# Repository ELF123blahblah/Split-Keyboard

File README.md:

## Hardware
# PCB

# Schematics

# Note
The bottom one and the little rectangle will be printed with transparent PLA. To give it an underglow effect and make a window for the microcontrollers
I have the screws thats why i didnt include it in the BOM.
## Details
This hackpad is made to help me have a better time while programming, gaming and 3D printing things.
### BOM
- 9 Cherry MX Switches
- 12 SK6812 MINI LEDs
- 1 XIAO RP2040
- 9 Blank DSA Keycaps
- ~ 80g Normal PLA
- ~ 30g transparent PLA
Disclaimer:
The switches and the top part fits perfectly because of some issues on my macbook I can't upload the video/image onto my github repo so if you have any questions please contact me via slack so that I can show you how it is made myself and answer any questions
### My request for the staff:
Please don't require a full component assembled photo/file as it is way too much work that I need to remove all the stuff to print it and it didn't make a difference in the aligning part as well cause i just had to flip the top part and that's it.

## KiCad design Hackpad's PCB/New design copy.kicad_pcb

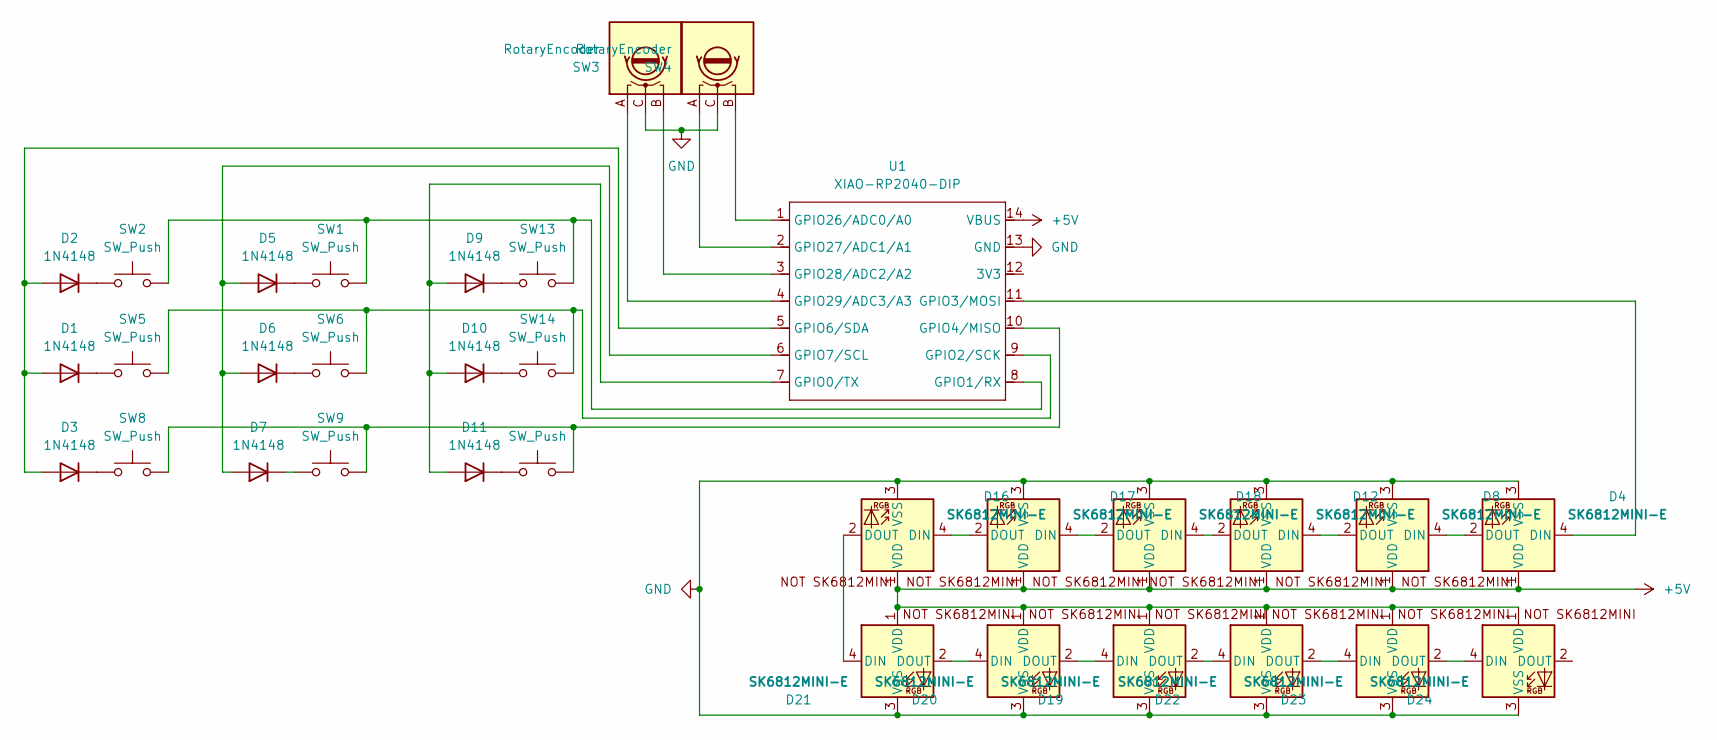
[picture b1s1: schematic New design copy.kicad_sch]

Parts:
D1, D2, D3, D5, D6, D7, D9, D10, D11: 1N4148; D_DO-35_SOD27_P7.62mm_Horizontal
D4, D8, D12, D16, D17, D18, D19, D20, D21, D22, D23, D24: SK6812MINI-E; SK6812MINI-E_fixed
SW1, SW2, SW5, SW6, SW8, SW9, SW13, SW14, SW15: SW_Push; SW_Cherry_MX_1.00u_PCB
SW3, SW4: RotaryEncoder; RotaryEncoder_Alps_EC11E_Vertical_H20mm
U1: XIAO-RP2040-DIP; XIAO-Generic-Hybrid-14P-2.54-21X17.8MM

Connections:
+5V: D4.1 (VDD), D8.1 (VDD), D12.1 (VDD), D16.1 (VDD), D17.1 (VDD), D18.1 (VDD), D19.1 (VDD), D20.1 (VDD), D21.1 (VDD), D22.1 (VDD), D23.1 (VDD), D24.1 (VDD), U1.14 (VBUS)
GND: D4.3 (VSS), D8.3 (VSS), D12.3 (VSS), D16.3 (VSS), D17.3 (VSS), D18.3 (VSS), D19.3 (VSS), D20.3 (VSS), D21.3 (VSS), D22.3 (VSS), D23.3 (VSS), D24.3 (VSS), SW3.C, SW4.C, U1.13 (GND)
unnamed: D1.2 (A), D2.2 (A), D3.2 (A), U1.5 (GPIO6/SDA)
unnamed: D1.1 (K), SW5.2
unnamed: D2.1 (K), SW2.2
unnamed: D3.1 (K), SW8.2
unnamed: D4.4 (DIN), U1.11 (GPIO3/MOSI)
unnamed: D4.2 (DOUT), D8.4 (DIN)
unnamed: D5.2 (A), D6.2 (A), D7.2 (A), U1.6 (GPIO7/SCL)
unnamed: D5.1 (K), SW1.2
unnamed: D6.1 (K), SW6.2
unnamed: D7.1 (K), SW9.2
unnamed: D9.1 (K), SW13.2
unnamed: D9.2 (A), D10.2 (A), D11.2 (A), U1.7 (GPIO0/TX)
unnamed: D10.1 (K), SW14.2
unnamed: D11.1 (K), SW15.2
unnamed: D8.2 (DOUT), D12.4 (DIN)
unnamed: D12.2 (DOUT), D18.4 (DIN)
unnamed: D16.4 (DIN), D17.2 (DOUT)
unnamed: D16.2 (DOUT), D21.4 (DIN)
unnamed: D17.4 (DIN), D18.2 (DOUT)
unnamed: D19.4 (DIN), D20.2 (DOUT)
unnamed: D19.2 (DOUT), D22.4 (DIN)
unnamed: D20.4 (DIN), D21.2 (DOUT)
unnamed: D22.2 (DOUT), D23.4 (DIN)
unnamed: D23.2 (DOUT), D24.4 (DIN)
unnamed: SW1.1, SW2.1, SW13.1, U1.8 (GPIO1/RX)
unnamed: SW5.1, SW6.1, SW14.1, U1.9 (GPIO2/SCK)
unnamed: SW8.1, SW9.1, SW15.1, U1.10 (GPIO4/MISO)
unnamed: SW4.B, U1.1 (GPIO26/ADC0/A0)
unnamed: SW4.A, U1.2 (GPIO27/ADC1/A1)
unnamed: SW3.B, U1.3 (GPIO28/ADC2/A2)
unnamed: SW3.A, U1.4 (GPIO29/ADC3/A3)

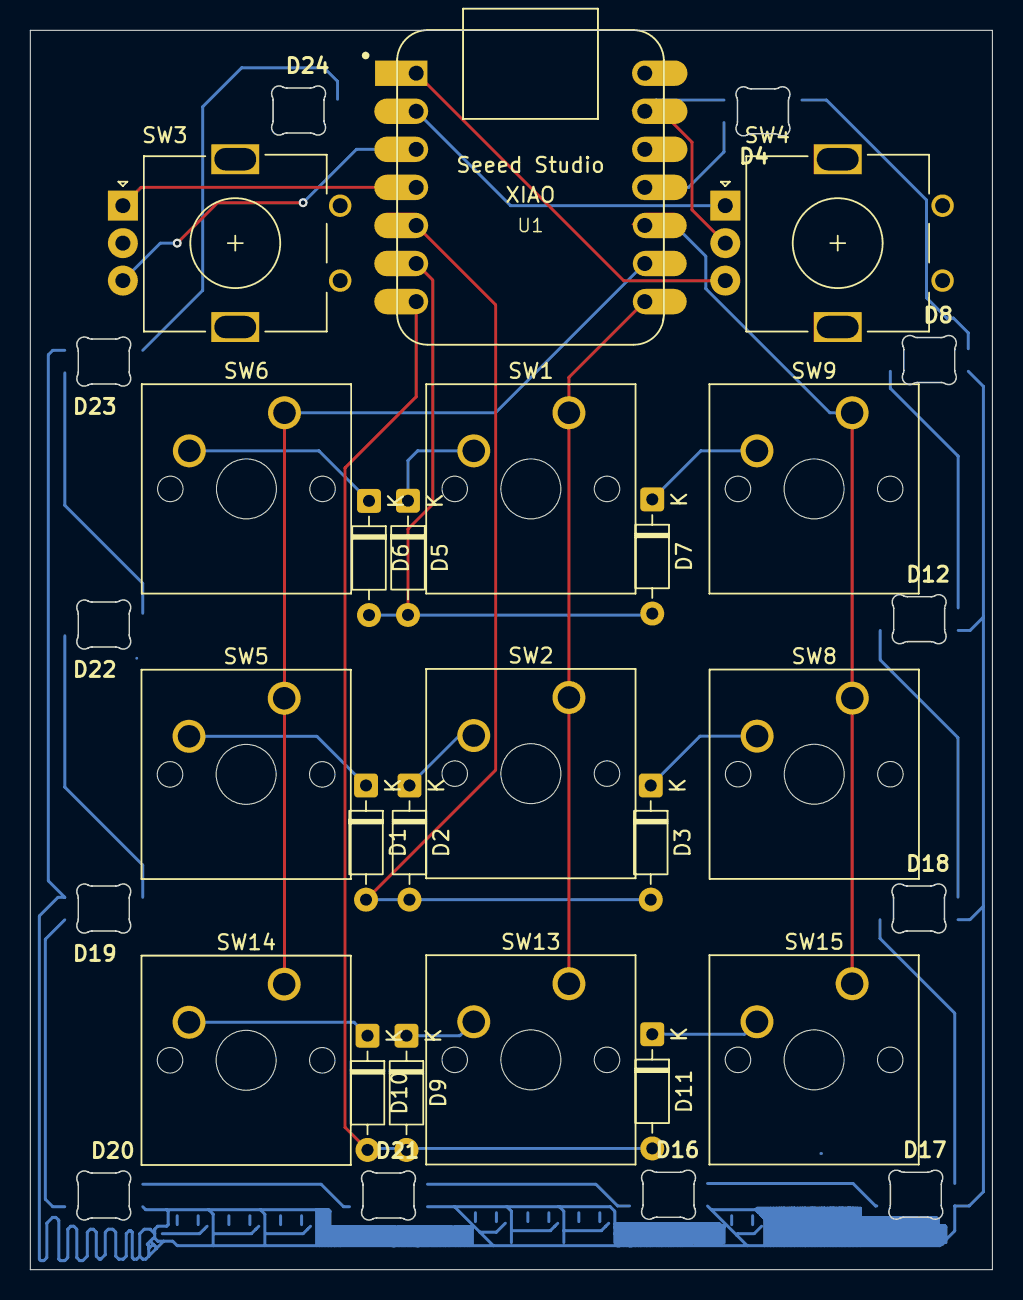
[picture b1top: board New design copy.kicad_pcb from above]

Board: 2 copper layers, 64.2 x 82.7 mm, 33 parts (0 on the bottom side), 33 nets.

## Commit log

2025-12-25 Enhance README with project purpose and Day 1 notes
    Expanded the README to include purpose and Day 1 learning experiences with Kicad.
2025-12-31 Revise project update for January 1, 2026
    Updated project notes for Day 8 with current status and challenges.
2026-01-11 Revise README with Hackpad details and images
    Updated README to include detailed sections on Hackpad components, firmware, and BOM.
2026-01-11 Revise README with new sections and images
    Updated README to include sections for Top, Middle, and Bottom images, and added details about firmware, schematics, and BOM.
2026-01-11 Programm
2026-01-14 Updated file
2026-01-15 Hopefully final
2026-01-15 Hopefully final V2
